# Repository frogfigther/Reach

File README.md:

# Reach
A repository containing the design files for the Reach board

Credit goes to Elias bakken for designing the basis of the reach, which we are now finishing 

(URL: http://bit.ly/2AH00zA)

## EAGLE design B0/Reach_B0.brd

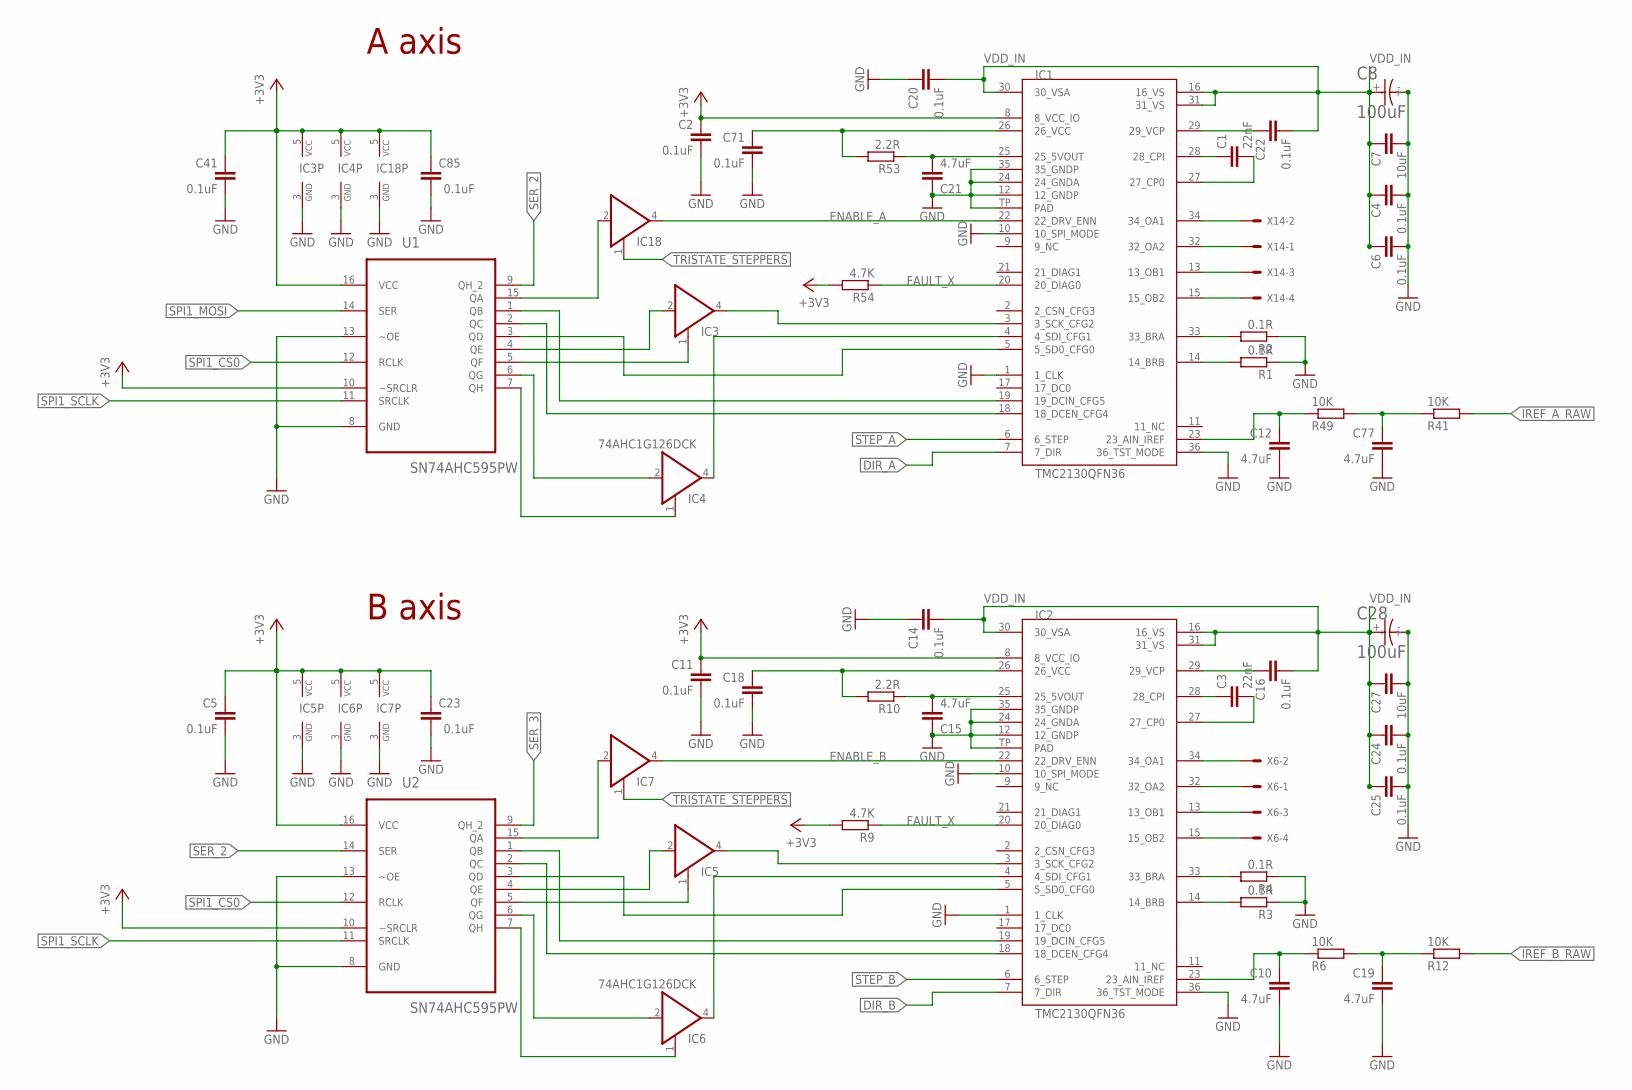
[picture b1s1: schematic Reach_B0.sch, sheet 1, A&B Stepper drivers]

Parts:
C1, C3: 22nF; C0402
C2, C5, C11, C14, C16, C18, C20, C22, C23, C41, C71, C85: 0.1uF; C0402
C4, C6, C24, C25: 0.1uF; C0402; MPN CL10B104KB8NNND
C7, C27: 10uF; C0805; MPN C2012X5R1V106M085AC
C8, C28: 100uF; RHS1V10MCN1GS; MPN RHS1V101MCN1GS
C10, C12, C15, C19, C21, C77: 4.7uF; C0402
IC1, IC2: TMC2130QFN36; QFN36
IC3, IC4, IC5, IC6, IC7, IC18: 74AHC1G126DCK; SC70-5
R1, R2, R3, R4: 0.1R; R0805
R6, R12, R41, R49: 10K; R0402
R9, R54: 4.7K; R0402
R10, R53: 2.2R; R0402
U1, U2: SN74AHC595PW; SOP65P640X120-16N
X6, X14: 22-05-7048-04; 7395-04

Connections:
+3V3: C2.1, C5.1, C11.1, C23.1, C41.1, C85.1, IC1.8 (8_VCC_IO), IC2.8 (8_VCC_IO), IC3.5 (VCC), IC4.5 (VCC), IC5.5 (VCC), IC6.5 (VCC), IC7.5 (VCC), IC18.5 (VCC), R9.2, R54.2, U1.10 (~SRCLR), U1.16 (VCC), U2.10 (~SRCLR), U2.16 (VCC); also elsewhere on the board
B_A3: IC2.34 (34_OA1), X6.2
B_A4: IC2.32 (32_OA2), X6.1
B_B3: IC2.15 (15_OB2), X6.4
B_B4: IC2.13 (13_OB1), X6.3
DIR_A: IC1.7 (7_DIR); also elsewhere on the board
DIR_B: IC2.7 (7_DIR); also elsewhere on the board
ENABLE_A: IC1.22 (22_DRV_ENN), IC18.4 (O)
ENABLE_B: IC2.22 (22_DRV_ENN), IC7.4 (O)
FAULT_X: IC1.20 (20_DIAG0), IC2.20 (20_DIAG0), R9.1, R54.1; also elsewhere on the board
GND: C2.2, C4.2, C5.2, C6.2, C7.2, C8.-, C10.2, C11.2, C12.2, C14.1, C15.1, C18.2, C19.2, C20.1, C21.1, C23.2, C24.2, C25.2, C27.2, C28.-, C41.2, C71.2, C77.2, C85.2, IC1.1 (1_CLK), IC1.10 (10_SPI_MODE), IC1.12 (12_GNDP), IC1.24 (24_GNDA), IC1.35 (35_GNDP), IC1.36 (36_TST_MODE), IC1.TP (PAD), IC2.1 (1_CLK), IC2.10 (10_SPI_MODE), IC2.12 (12_GNDP), IC2.24 (24_GNDA), IC2.35 (35_GNDP), IC2.36 (36_TST_MODE), IC2.TP (PAD), IC3.3 (GND), IC4.3 (GND), IC5.3 (GND), IC6.3 (GND), IC7.3 (GND), IC18.3 (GND), R1.1, R2.1, R3.1, R4.1, U1.8 (GND), U1.13 (~OE), U2.8 (GND), U2.13 (~OE); also elsewhere on the board
IREF_A: C77.1, R41.1, R49.2
IREF_A_RAW: R41.2; also elsewhere on the board
IREF_B: C19.1, R6.2, R12.1
IREF_B_RAW: R12.2; also elsewhere on the board
unnamed: C3.2, IC2.27 (27_CP0)
unnamed: IC2.14 (14_BRB), R3.2
unnamed: IC2.33 (33_BRA), R4.2
unnamed: IC4.1 (OE), U1.7 (QH)
unnamed: IC4.2 (I), U1.6 (QG)
unnamed: IC1.18 (18_DCEN_CFG4), U1.2 (QC)
unnamed: C1.1, IC1.28 (28_CPI)
unnamed: C1.2, IC1.27 (27_CP0)
unnamed: IC1.14 (14_BRB), R1.2
unnamed: IC1.33 (33_BRA), R2.2
unnamed: C12.1, IC1.23 (23_AIN_IREF), R49.1
unnamed: C10.1, IC2.23 (23_AIN_IREF), R6.1
unnamed: C3.1, IC2.28 (28_CPI)
unnamed: C15.2, IC2.25 (25_5VOUT), R10.1
unnamed: C16.1, IC2.29 (29_VCP)
unnamed: IC2.18 (18_DCEN_CFG4), U2.2 (QC)
unnamed: IC2.19 (19_DCIN_CFG5), U2.1 (QB)
unnamed: IC6.1 (OE), U2.7 (QH)
unnamed: IC6.2 (I), U2.6 (QG)
unnamed: IC5.2 (I), U2.4 (QE)
unnamed: C21.2, IC1.25 (25_5VOUT), R53.1
unnamed: IC5.1 (OE), U2.5 (QF)
unnamed: C22.1, IC1.29 (29_VCP)
unnamed: IC3.2 (I), U1.4 (QE)
unnamed: IC2.5 (5_SD0_CFG0), U2.3 (QD)
unnamed: C18.1, IC2.26 (26_VCC), R10.2
unnamed: IC7.2 (I), U2.15 (QA)
unnamed: IC3.1 (OE), U1.5 (QF)
unnamed: IC1.19 (19_DCIN_CFG5), U1.1 (QB)
unnamed: IC1.5 (5_SD0_CFG0), U1.3 (QD)
unnamed: C71.1, IC1.26 (26_VCC), R53.2
unnamed: IC18.2 (I), U1.15 (QA)
SER_2: U1.9 (QH_2), U2.14 (SER)
SER_3: U2.9 (QH_2); also elsewhere on the board
SPI1_CS0: U1.12 (RCLK), U2.12 (RCLK); also elsewhere on the board
SPI1_MOSI: U1.14 (SER); also elsewhere on the board
SPI1_SCLK: U1.11 (SRCLK), U2.11 (SRCLK); also elsewhere on the board
STEP_A: IC1.6 (6_STEP); also elsewhere on the board
STEP_B: IC2.6 (6_STEP); also elsewhere on the board
TRISTATE_STEPPERS: IC7.1 (OE), IC18.1 (OE); also elsewhere on the board
VDD_IN: C4.1, C6.1, C7.1, C8.+, C14.2, C16.2, C20.2, C22.2, C24.1, C25.1, C27.1, C28.+, IC1.16 (16_VS), IC1.30 (30_VSA), IC1.31 (31_VS), IC2.16 (16_VS), IC2.30 (30_VSA), IC2.31 (31_VS); also elsewhere on the board
X_A1: IC1.34 (34_OA1), X14.2
X_A2: IC1.32 (32_OA2), X14.1
X_B1: IC1.13 (13_OB1), X14.3
X_B2: IC1.15 (15_OB2), X14.4
X_CFG1: IC1.4 (4_SDI_CFG1), IC4.4 (O)
X_CFG2: IC1.3 (3_SCK_CFG2), IC3.4 (O)
X_CFG3: IC2.3 (3_SCK_CFG2), IC5.4 (O)
X_CFG4: IC2.4 (4_SDI_CFG1), IC6.4 (O)

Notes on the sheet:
A axis
B axis

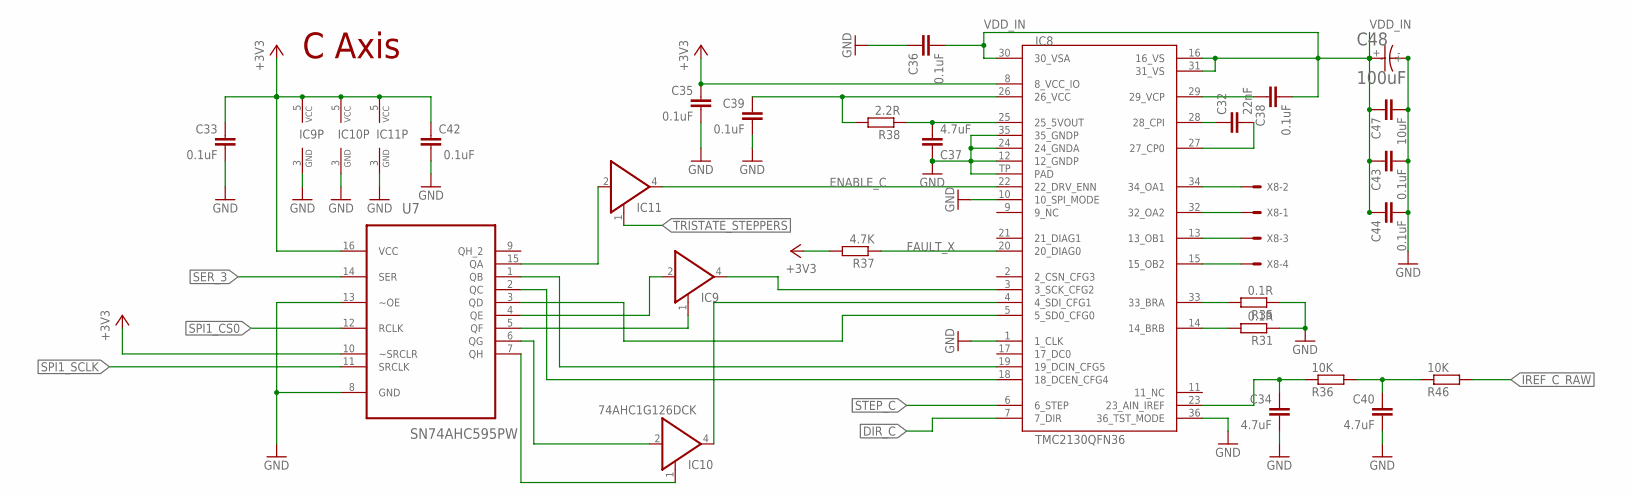
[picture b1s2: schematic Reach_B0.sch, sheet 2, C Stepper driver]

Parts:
C32: 22nF; C0402
C33, C35, C36, C38, C39, C42: 0.1uF; C0402
C34, C37, C40: 4.7uF; C0402
C43, C44: 0.1uF; C0402; MPN CL10B104KB8NNND
C47: 10uF; C0805; MPN C2012X5R1V106M085AC
C48: 100uF; RHS1V10MCN1GS; MPN RHS1V101MCN1GS
IC8: TMC2130QFN36; QFN36
IC9, IC10, IC11: 74AHC1G126DCK; SC70-5
R31, R35: 0.1R; R0805
R36, R46: 10K; R0402
R37: 4.7K; R0402
R38: 2.2R; R0402
U7: SN74AHC595PW; SOP65P640X120-16N
X8: 22-05-7048-04; 7395-04

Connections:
+3V3: C33.1, C35.1, C42.1, IC8.8 (8_VCC_IO), IC9.5 (VCC), IC10.5 (VCC), IC11.5 (VCC), R37.2, U7.10 (~SRCLR), U7.16 (VCC); also elsewhere on the board
C_A3: IC8.34 (34_OA1), X8.2
C_A4: IC8.32 (32_OA2), X8.1
C_B3: IC8.15 (15_OB2), X8.4
C_B4: IC8.13 (13_OB1), X8.3
DIR_C: IC8.7 (7_DIR); also elsewhere on the board
ENABLE_C: IC8.22 (22_DRV_ENN), IC11.4 (O)
FAULT_X: IC8.20 (20_DIAG0), R37.1; also elsewhere on the board
GND: C33.2, C34.2, C35.2, C36.1, C37.1, C39.2, C40.2, C42.2, C43.2, C44.2, C47.2, C48.-, IC8.1 (1_CLK), IC8.10 (10_SPI_MODE), IC8.12 (12_GNDP), IC8.24 (24_GNDA), IC8.35 (35_GNDP), IC8.36 (36_TST_MODE), IC8.TP (PAD), IC9.3 (GND), IC10.3 (GND), IC11.3 (GND), R31.1, R35.1, U7.8 (GND), U7.13 (~OE); also elsewhere on the board
IREF_C: C40.1, R36.2, R46.1
IREF_C_RAW: R46.2; also elsewhere on the board
unnamed: C32.2, IC8.27 (27_CP0)
unnamed: IC8.14 (14_BRB), R31.2
unnamed: IC8.33 (33_BRA), R35.2
unnamed: C34.1, IC8.23 (23_AIN_IREF), R36.1
unnamed: C32.1, IC8.28 (28_CPI)
unnamed: C37.2, IC8.25 (25_5VOUT), R38.1
unnamed: C38.1, IC8.29 (29_VCP)
unnamed: IC8.18 (18_DCEN_CFG4), U7.2 (QC)
unnamed: IC8.19 (19_DCIN_CFG5), U7.1 (QB)
unnamed: IC10.1 (OE), U7.7 (QH)
unnamed: IC10.2 (I), U7.6 (QG)
unnamed: IC9.2 (I), U7.4 (QE)
unnamed: IC9.1 (OE), U7.5 (QF)
unnamed: IC8.5 (5_SD0_CFG0), U7.3 (QD)
unnamed: C39.1, IC8.26 (26_VCC), R38.2
unnamed: IC11.2 (I), U7.15 (QA)
SER_3: U7.14 (SER); also elsewhere on the board
SPI1_CS0: U7.12 (RCLK); also elsewhere on the board
SPI1_SCLK: U7.11 (SRCLK); also elsewhere on the board
STEP_C: IC8.6 (6_STEP); also elsewhere on the board
TRISTATE_STEPPERS: IC11.1 (OE); also elsewhere on the board
VDD_IN: C36.2, C38.2, C43.1, C44.1, C47.1, C48.+, IC8.16 (16_VS), IC8.30 (30_VSA), IC8.31 (31_VS); also elsewhere on the board
X_CFG5: IC8.3 (3_SCK_CFG2), IC9.4 (O)
X_CFG6: IC8.4 (4_SDI_CFG1), IC10.4 (O)

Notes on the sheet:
C Axis

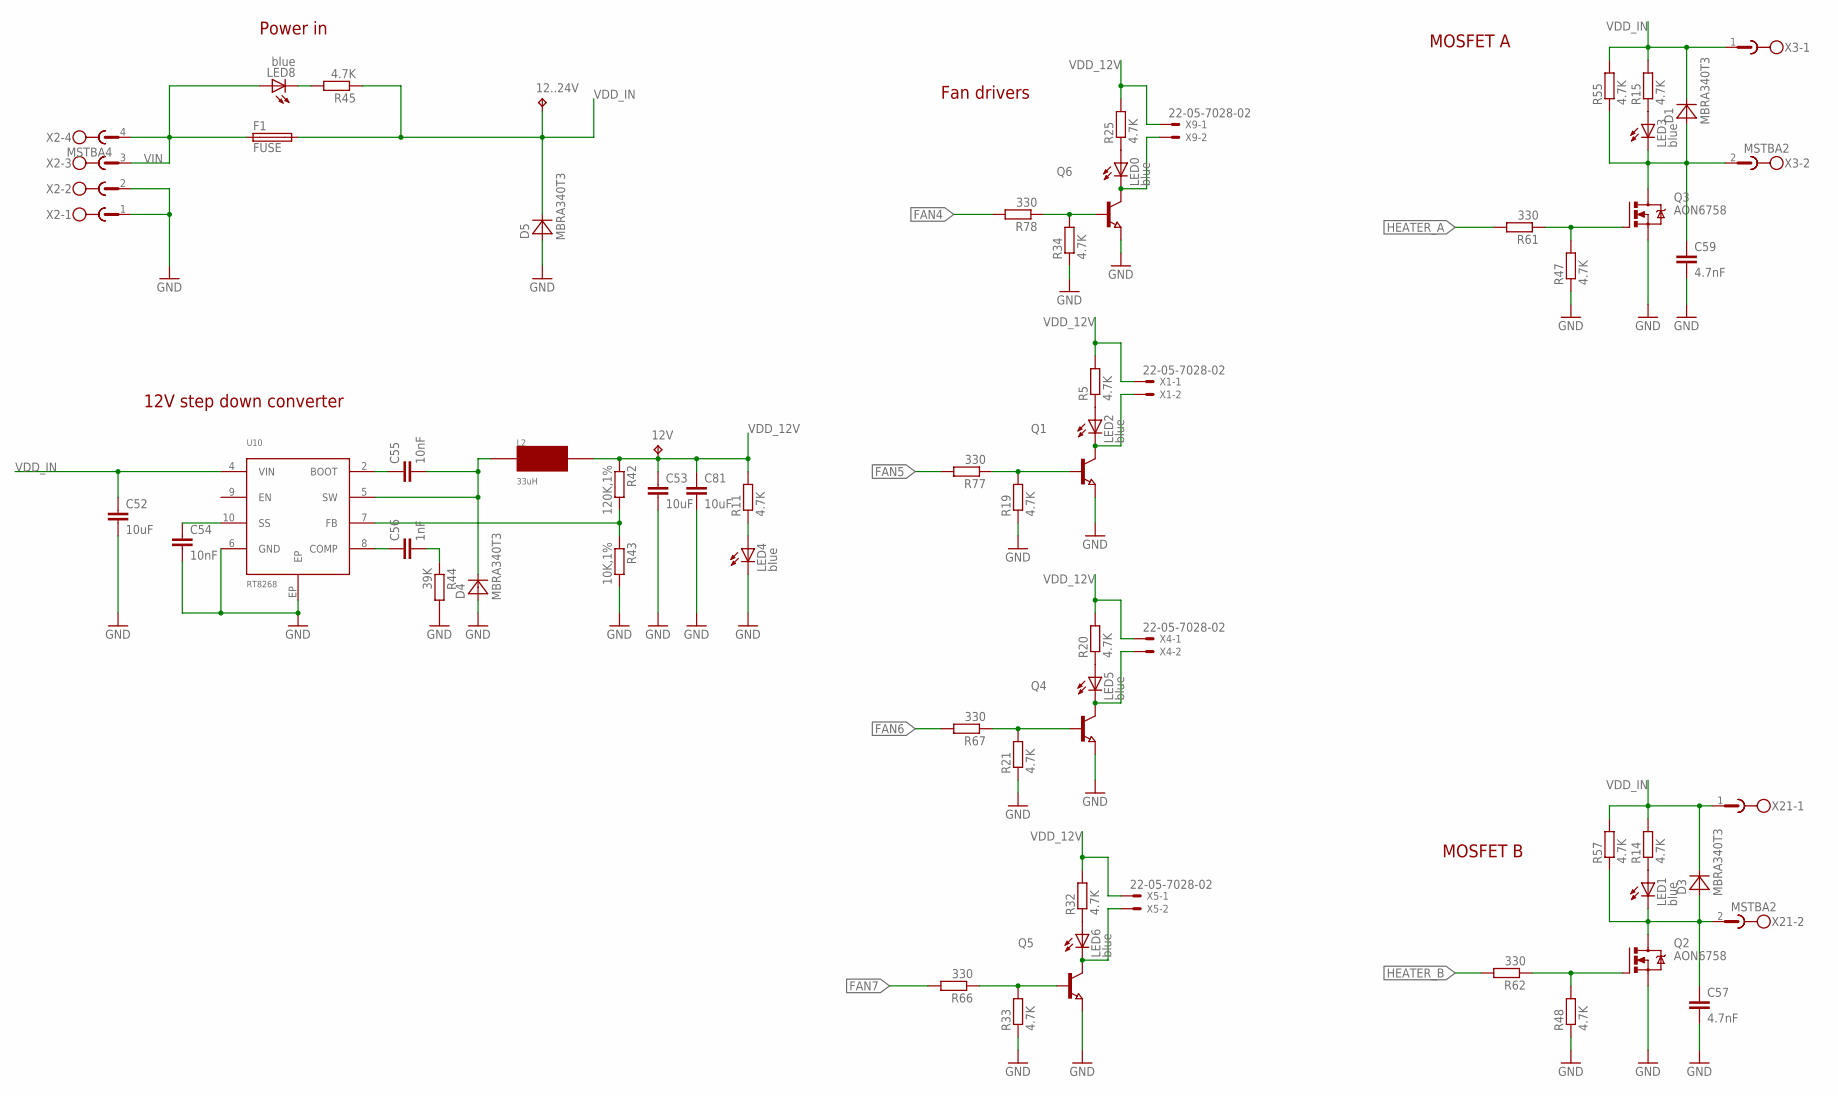
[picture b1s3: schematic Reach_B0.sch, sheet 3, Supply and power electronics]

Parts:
12..24V, 12V: TPB1,27; B1,27
C52, C53, C81: 10uF; C1206; MPN CL31B106KAHNNNE
C54, C55: 10nF; C0402; MPN CL05B103KB5NNNC
C56: 1nF; C0402; MPN C1005X7R1H102K050BA
C57, C59: 4.7nF; C0402
D1, D3, D5: MBRA340T3; SMA
D4: MBRA340T3; SMA; MPN MBRA340T3G
F1: FUSE; 3557
L2: 33uH; NR8040T330; MPN NR8040T330M
LED0, LED2, LED4, LED5, LED6: blue; CHIP-LED0603; MPN Q65110A7211
LED1, LED3, LED8: blue; CHIP-LED0603
Q1, Q4, Q5, Q6: NPN-TRANSISTOR_SOT23; SOT23; MPN AO7400
Q2, Q3: AON6758; 8-DFN-EP-(5X6)
R5, R11, R19, R20, R21, R25, R32, R33, R34: 4.7K; R0402; MPN RC0402JR-074K7L
R14, R15, R45, R47, R48, R55, R57: 4.7K; R0402
R42: 120K,1%; R0402; MPN RMCF0402FT120K
R43: 10K,1%; R0402; MPN RC0402FR-0710KL
R44: 39K; R0402; MPN RC1005J393CS
R61, R62, R66, R67, R77, R78: 330; R0402
U10: RT8268; MSOP10; MPN RT8268GFP
X1, X4, X5, X9: 22-05-7028-02; 7395-02; MPN 640455-2
X2: MSTBA4
X3, X21: MSTBA2

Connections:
FAN4: R78.2; also elsewhere on the board
FAN5: R77.2; also elsewhere on the board
FAN6: R67.2; also elsewhere on the board
FAN7: R66.2; also elsewhere on the board
GND: C52.2, C53.2, C54.2, C57.2, C59.2, C81.2, D4.A, D5.A, LED4.C, Q1.2 (E), Q2.1 (S), Q2.2 (S), Q2.3 (S), Q3.1 (S), Q3.2 (S), Q3.3 (S), Q4.2 (E), Q5.2 (E), Q6.2 (E), R19.1, R21.1, R33.1, R34.1, R43.2, R44.2, R47.1, R48.1, U10.6 (GND), U10.EP, X2.1, X2.2; also elsewhere on the board
HEATER_A: R61.2; also elsewhere on the board
HEATER_B: R62.2; also elsewhere on the board
unnamed: LED8.C, R45.2
unnamed: LED2.C, Q1.3 (C), X1.2
unnamed: LED0.C, Q6.3 (C), X9.2
unnamed: LED0.A, R25.1
unnamed: Q3.4 (G), R47.2, R61.1
unnamed: C57.1, D3.A, LED1.C, Q2.5 (D), Q2.6 (D), Q2.7 (D), Q2.8 (D), Q2.TH (D), R57.1, X21.2
unnamed: Q2.4 (G), R48.2, R62.1
unnamed: Q5.1 (B), R33.2, R66.1
unnamed: Q4.1 (B), R21.2, R67.1
unnamed: LED2.A, R5.1
unnamed: LED5.C, Q4.3 (C), X4.2
unnamed: LED5.A, R20.1
unnamed: LED6.C, Q5.3 (C), X5.2
unnamed: LED6.A, R32.1
unnamed: Q1.1 (B), R19.2, R77.1
unnamed: Q6.1 (B), R34.2, R78.1
unnamed: LED4.A, R11.1
unnamed: LED3.A, R15.1
unnamed: LED1.A, R14.1
unnamed: R42.2, R43.1, U10.7 (FB)
unnamed: C59.1, D1.A, LED3.C, Q3.5 (D), Q3.6 (D), Q3.7 (D), Q3.8 (D), Q3.TH (D), R55.1, X3.2
unnamed: C55.2, D4.C, L2.P$2, U10.5 (SW)
unnamed: C54.1, U10.10 (SS)
unnamed: C56.1, U10.8 (COMP)
unnamed: C55.1, U10.2 (BOOT)
unnamed: C56.2, R44.1
VDD_12V: 12V.TP, C53.1, C81.1, L2.P$1, R5.2, R11.2, R20.2, R25.2, R32.2, R42.1, X1.1, X4.1, X5.1, X9.1
VDD_IN: 12..24V.TP, C52.1, D1.C, D3.C, D5.C, F1.P$3 (2), F1.P$4 (2), R14.2, R15.2, R45.1, R55.2, R57.2, U10.4 (VIN), X3.1, X21.1; also elsewhere on the board
VIN: F1.P$1 (1), F1.P$2 (1), LED8.A, X2.3, X2.4

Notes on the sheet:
Power in
MOSFET A
MOSFET B
12V step down converter
Fan drivers

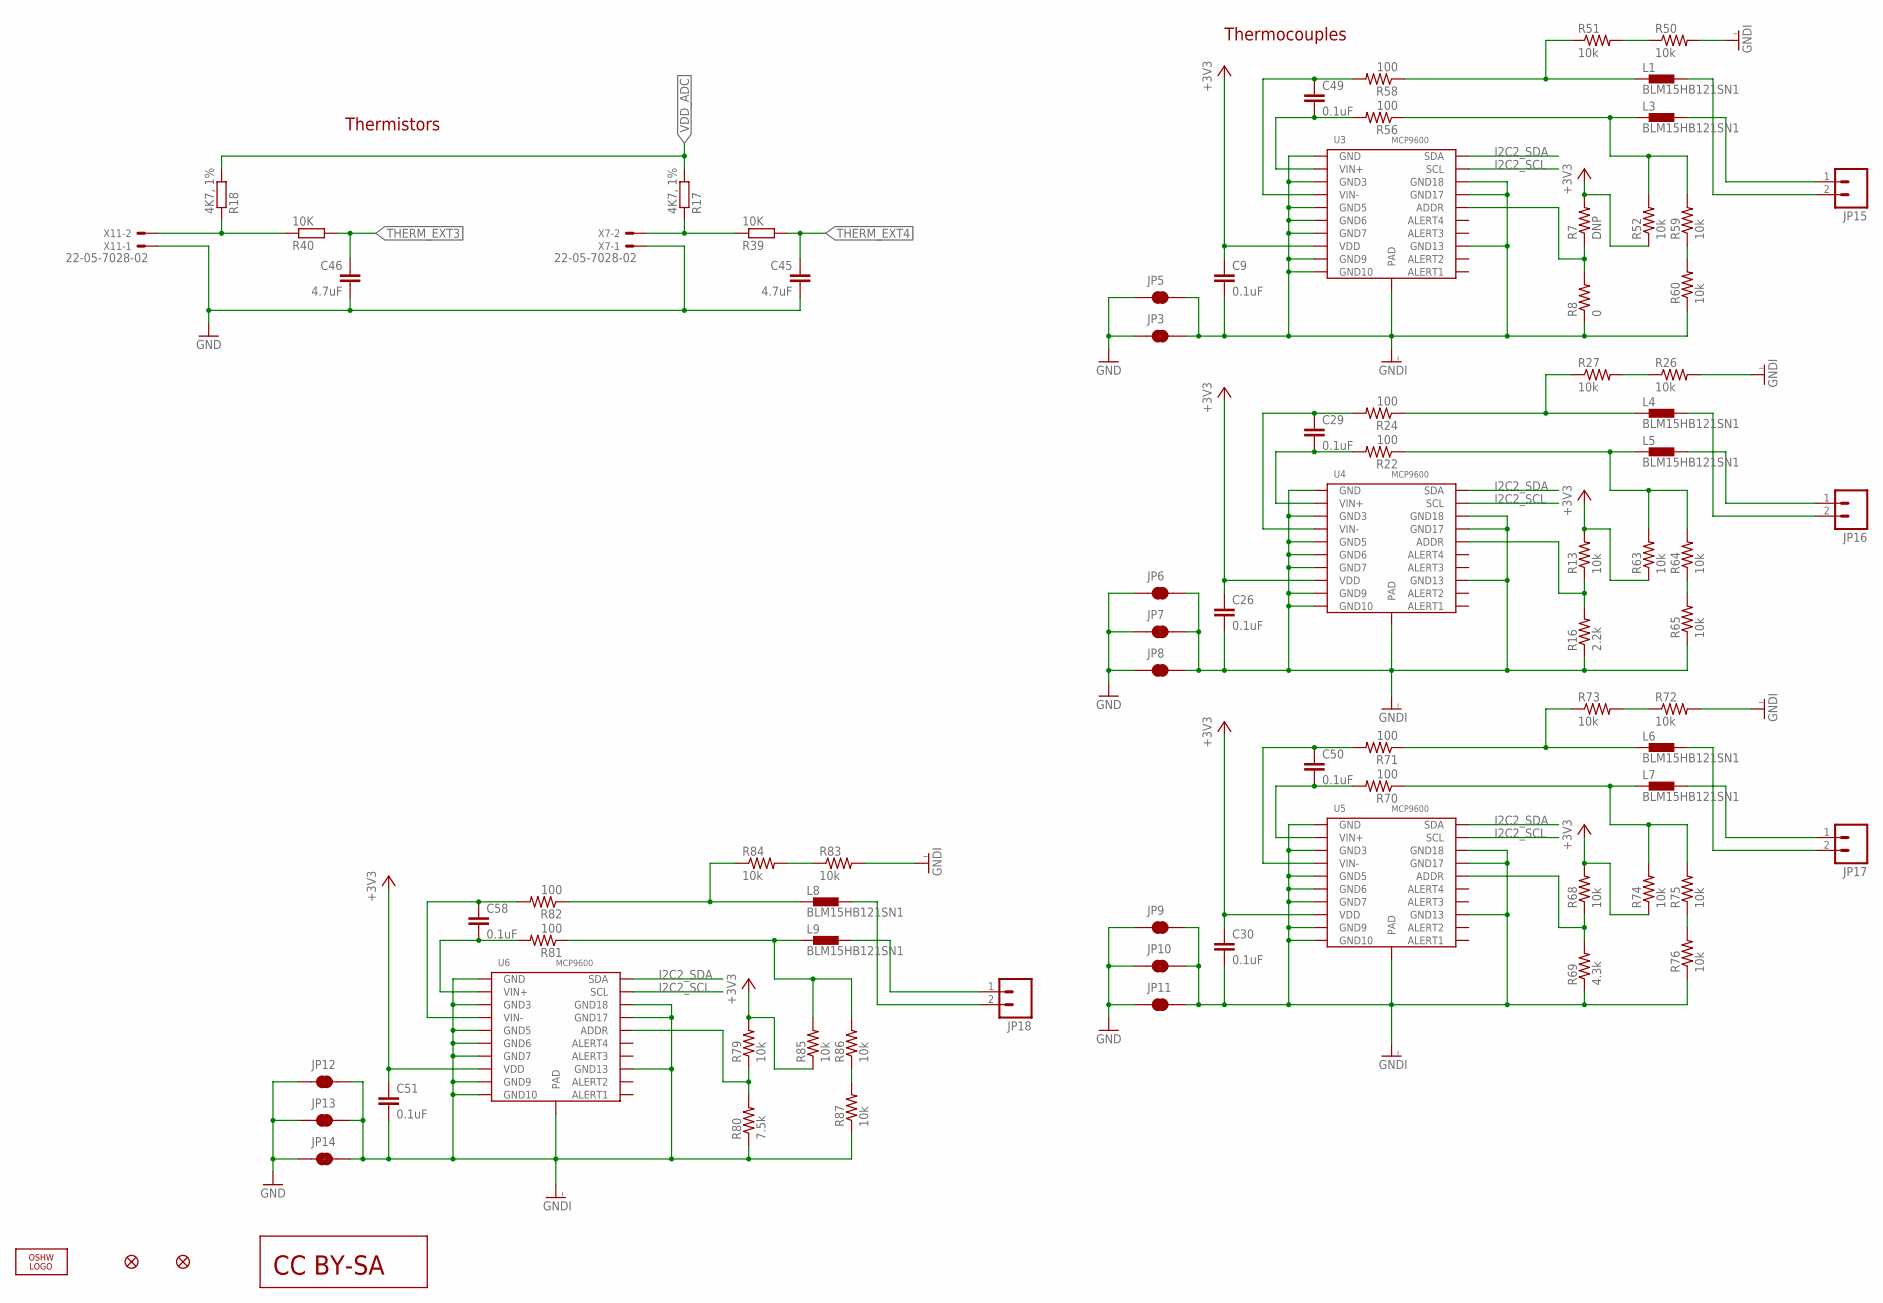
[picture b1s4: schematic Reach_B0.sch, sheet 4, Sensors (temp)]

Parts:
C9, C26, C29, C30, C49, C50, C51, C58: 0.1uF; C0402
C45, C46: 4.7uF; C0402; MPN GRM155R60J475ME47D
JP1, JP2: FIDUCIAL1X2.5; FIDUCIAL-1X2.5
JP3, JP5, JP6, JP7, JP8, JP9, JP10, JP11, JP12, JP13, JP14: JUMPER-PAD-2-NC_BY_TRACE; PAD-JUMPER-2-NC_BY_TRACE_YES_SILK
JP15, JP16, JP17, JP18: M025MM; SCREWTERMINAL-5MM-2
L1, L3, L4, L5, L6, L7, L8, L9: BLM15HB121SN1; 0402
LOGO1: OSHW_LOGO_FILLX0200-NT; OSHW_FILLX200_NOTEXT
R7: DNP; 0402-RES
R8: 0; 0402-RES
R13, R68, R79: 10k; 0402-RES
R16: 2.2k; 0402-RES
R17, R18: 4K7, 1%; R0402; MPN RC0402FR-074K7L
R22, R24, R56, R58, R70, R71, R81, R82: 100; 0402-RES
R26, R27, R50, R51, R52, R59, R60, R63, R64, R65, R72, R73, R74, R75, R76, R83, R84, R85, R86, R87: 10k; 0805
R39, R40: 10K; R0402; MPN RC0402FR-0710KL
R69: 4.3k; 0402-RES
R80: 7.5k; 0402-RES
U3, U4, U5, U6: MCP9600; MQFN-20
U$4: CC-BY-SA
X7, X11: 22-05-7028-02; 7395-02; MPN 640455-2

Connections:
+3V3: C9.1, C26.1, C30.1, C51.1, R7.2, R13.2, R52.1, R63.1, R68.2, R74.1, R79.2, R85.1, U3.P$8 (VDD), U4.P$8 (VDD), U5.P$8 (VDD), U6.P$8 (VDD); also elsewhere on the board
GND: C45.2, C46.2, JP3.1, JP5.1, JP6.1, JP7.1, JP8.1, JP9.1, JP10.1, JP11.1, JP12.1, JP13.1, JP14.1, X7.1, X11.1; also elsewhere on the board
GNDI: C9.2, C26.2, C30.2, C51.2, JP3.2, JP5.2, JP6.2, JP7.2, JP8.2, JP9.2, JP10.2, JP11.2, JP12.2, JP13.2, JP14.2, R8.1, R16.1, R26.2, R50.2, R60.1, R65.1, R69.1, R72.2, R76.1, R80.1, R83.2, R87.1, U3.P$1 (GND), U3.P$3 (GND3), U3.P$5 (GND5), U3.P$6 (GND6), U3.P$7 (GND7), U3.P$9 (GND9), U3.P$10 (GND10), U3.P$13 (GND13), U3.P$17 (GND17), U3.P$18 (GND18), U3.P$21 (PAD), U4.P$1 (GND), U4.P$3 (GND3), U4.P$5 (GND5), U4.P$6 (GND6), U4.P$7 (GND7), U4.P$9 (GND9), U4.P$10 (GND10), U4.P$13 (GND13), U4.P$17 (GND17), U4.P$18 (GND18), U4.P$21 (PAD), U5.P$1 (GND), U5.P$3 (GND3), U5.P$5 (GND5), U5.P$6 (GND6), U5.P$7 (GND7), U5.P$9 (GND9), U5.P$10 (GND10), U5.P$13 (GND13), U5.P$17 (GND17), U5.P$18 (GND18), U5.P$21 (PAD), U6.P$1 (GND), U6.P$3 (GND3), U6.P$5 (GND5), U6.P$6 (GND6), U6.P$7 (GND7), U6.P$9 (GND9), U6.P$10 (GND10), U6.P$13 (GND13), U6.P$17 (GND17), U6.P$18 (GND18), U6.P$21 (PAD)
I2C2_SCL: U3.P$19 (SCL), U4.P$19 (SCL), U5.P$19 (SCL), U6.P$19 (SCL); also elsewhere on the board
I2C2_SDA: U3.P$20 (SDA), U4.P$20 (SDA), U5.P$20 (SDA), U6.P$20 (SDA); also elsewhere on the board
unnamed: R50.1, R51.2
unnamed: L3.1, R52.2, R56.1, R59.2
unnamed: JP15.1, L3.2
unnamed: JP15.2, L1.2
unnamed: JP16.2, L4.2
unnamed: R7.1, R8.2, U3.P$16 (ADDR)
unnamed: R13.1, R16.2, U4.P$16 (ADDR)
unnamed: L5.1, R22.1, R63.2, R64.2
unnamed: C29.2, R22.2, U4.P$2 (VIN+)
unnamed: C29.1, R24.2, U4.P$4 (VIN-)
unnamed: JP16.1, L5.2
unnamed: L4.1, R24.1, R27.1
unnamed: R26.1, R27.2
unnamed: R64.1, R65.2
unnamed: C49.2, R56.2, U3.P$2 (VIN+)
unnamed: C49.1, R58.2, U3.P$4 (VIN-)
unnamed: L1.1, R51.1, R58.1
unnamed: R59.1, R60.2
unnamed: JP17.2, L6.2
unnamed: R68.1, R69.2, U5.P$16 (ADDR)
unnamed: L7.1, R70.1, R74.2, R75.2
unnamed: C50.2, R70.2, U5.P$2 (VIN+)
unnamed: C50.1, R71.2, U5.P$4 (VIN-)
unnamed: JP17.1, L7.2
unnamed: L6.1, R71.1, R73.1
unnamed: R72.1, R73.2
unnamed: R75.1, R76.2
unnamed: JP18.2, L8.2
unnamed: R79.1, R80.2, U6.P$16 (ADDR)
unnamed: L9.1, R81.1, R85.2, R86.2
unnamed: C58.2, R81.2, U6.P$2 (VIN+)
unnamed: C58.1, R82.2, U6.P$4 (VIN-)
unnamed: JP18.1, L9.2
unnamed: L8.1, R82.1, R84.1
unnamed: R83.1, R84.2
unnamed: R86.1, R87.2
unnamed: R18.1, R40.1, X11.2
unnamed: R17.1, R39.1, X7.2
THERM_EXT3: C46.1, R40.2; also elsewhere on the board
THERM_EXT4: C45.1, R39.2; also elsewhere on the board
VDD_ADC: R17.2, R18.2; also elsewhere on the board

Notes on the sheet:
Thermistors
Thermocouples

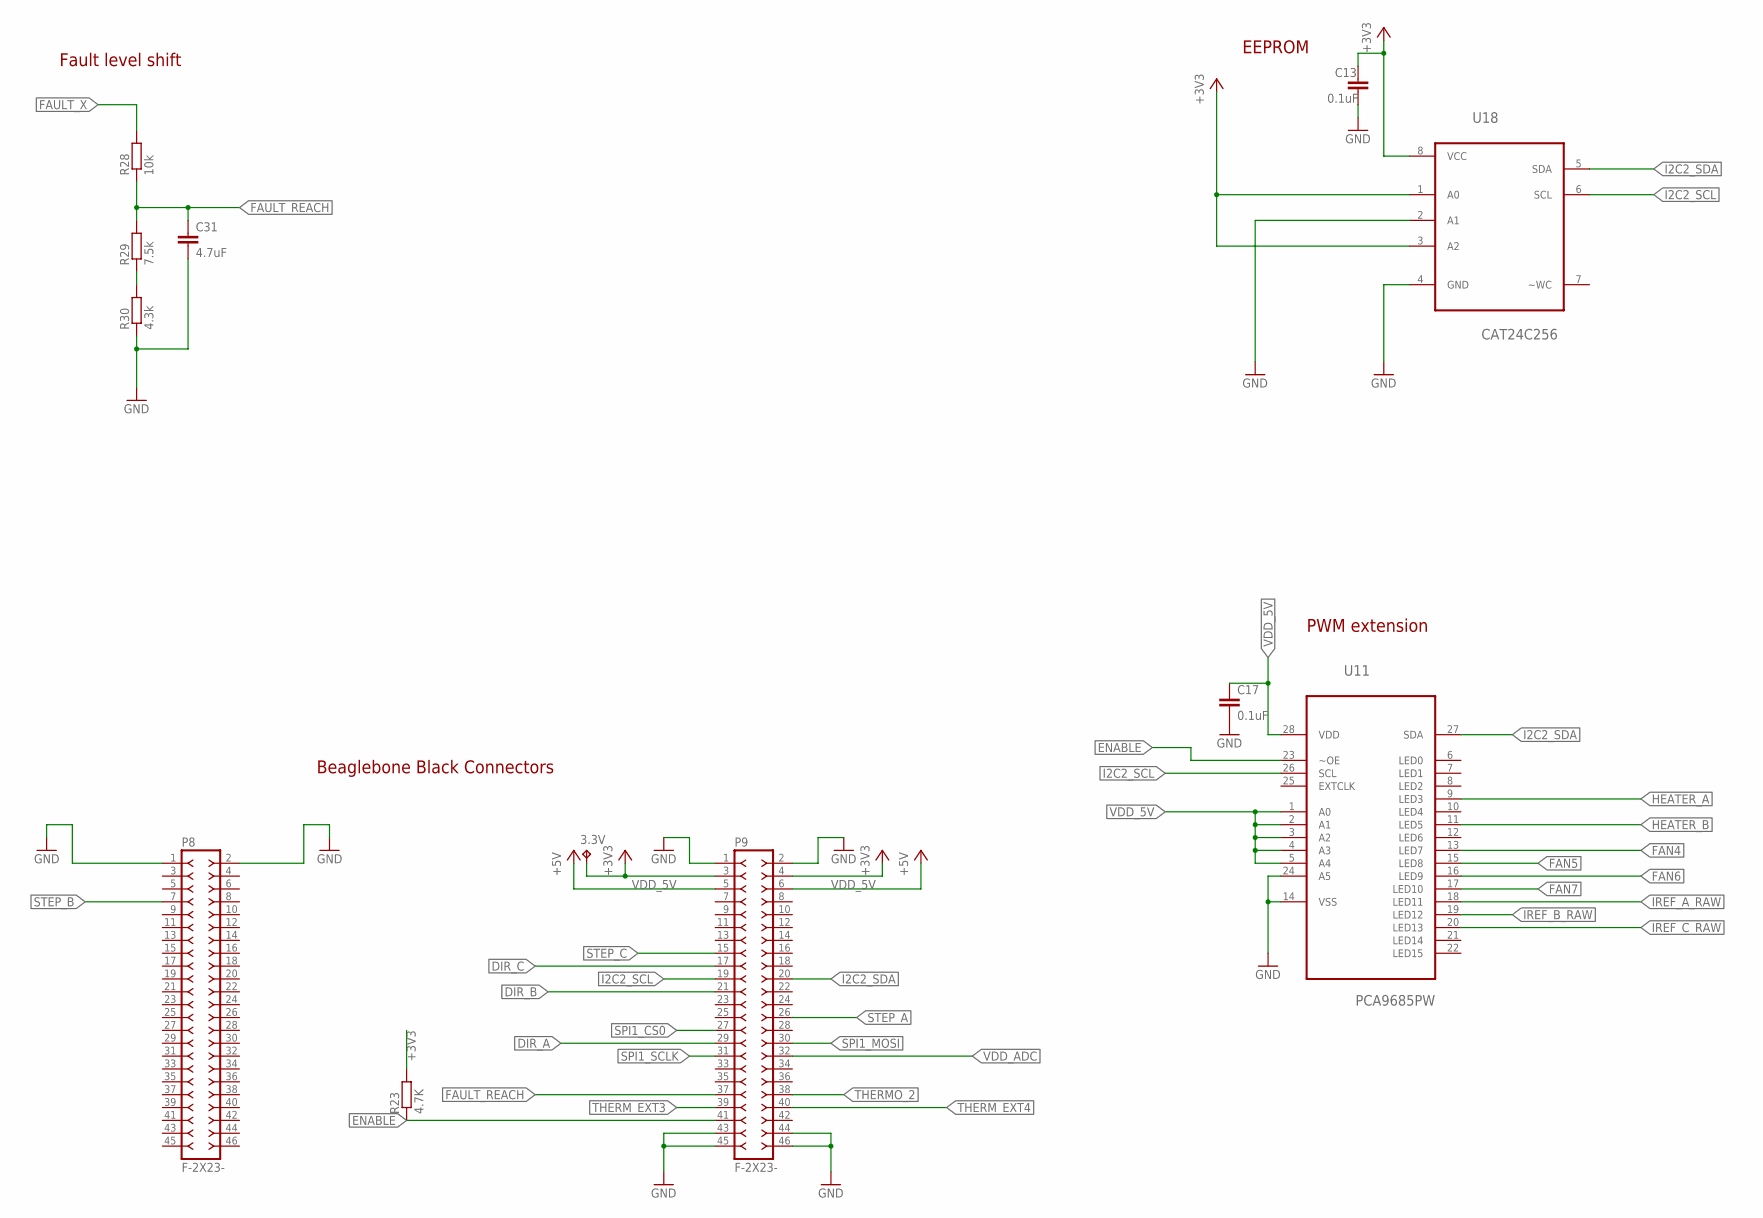
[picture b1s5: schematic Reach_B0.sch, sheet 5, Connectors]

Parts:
3.3V: TPB1,27; B1,27
C13, C17: 0.1uF; C0402
C31: 4.7uF; C0402
P8, P9: F-2X23-; DIL-100-2X23
R23: 4.7K; R0402
R28: 10k; R0402
R29: 7.5k; R0402
R30: 4.3k; R0402
U11: PCA9685PW; SOP65P640X110-28N
U18: CAT24C256; SOIC127P600X175-8N

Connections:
+3V3: 3.3V.TP, C13.1, P9.3, P9.4, R23.2, U18.1 (A0), U18.3 (A2), U18.8 (VCC); also elsewhere on the board
DIR_A: P9.29; also elsewhere on the board
DIR_B: P9.21; also elsewhere on the board
DIR_C: P9.17; also elsewhere on the board
ENABLE: P9.41, R23.1, U11.23 (~OE)
FAN4: U11.13 (LED7); also elsewhere on the board
FAN5: U11.15 (LED8); also elsewhere on the board
FAN6: U11.16 (LED9); also elsewhere on the board
FAN7: U11.17 (LED10); also elsewhere on the board
FAULT_REACH: C31.1, P9.37, R28.1, R29.2
FAULT_X: R28.2; also elsewhere on the board
GND: C13.2, C17.2, C31.2, P8.1, P8.2, P9.1, P9.2, P9.43, P9.44, P9.45, P9.46, R30.1, U11.14 (VSS), U11.24 (A5), U18.2 (A1), U18.4 (GND); also elsewhere on the board
HEATER_A: U11.9 (LED3); also elsewhere on the board
HEATER_B: U11.11 (LED5); also elsewhere on the board
I2C2_SCL: P9.19, U11.26 (SCL), U18.6 (SCL); also elsewhere on the board
I2C2_SDA: P9.20, U11.27 (SDA), U18.5 (SDA); also elsewhere on the board
IREF_A_RAW: U11.18 (LED11); also elsewhere on the board
IREF_B_RAW: U11.19 (LED12); also elsewhere on the board
IREF_C_RAW: U11.20 (LED13); also elsewhere on the board
unnamed: R29.1, R30.2
SPI1_CS0: P9.27; also elsewhere on the board
SPI1_MOSI: P9.30; also elsewhere on the board
SPI1_SCLK: P9.31; also elsewhere on the board
STEP_A: P9.26; also elsewhere on the board
STEP_B: P8.7; also elsewhere on the board
STEP_C: P9.15; also elsewhere on the board
THERMO_2: P9.38
THERM_EXT3: P9.39; also elsewhere on the board
THERM_EXT4: P9.40; also elsewhere on the board
VDD_5V: C17.1, P9.5, P9.6, U11.1 (A0), U11.2 (A1), U11.3 (A2), U11.4 (A3), U11.5 (A4), U11.28 (VDD)
VDD_ADC: P9.32; also elsewhere on the board

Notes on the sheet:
EEPROM
Fault level shift
Beaglebone Black Connectors
PWM extension

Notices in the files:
parts and their libraries:
con-headers-jp: Copyright (C) 2008, Bob Starr
SparkFun-Resistors: Licensing: CC v3.0 Share-Alike You are welcome to use this library for commercial purposes.
SparkFun-PassivesNEW: Licensing: Creative Commons ShareAlike 4.0 International - https://creativecommons.org/licenses/by-sa/4.0
